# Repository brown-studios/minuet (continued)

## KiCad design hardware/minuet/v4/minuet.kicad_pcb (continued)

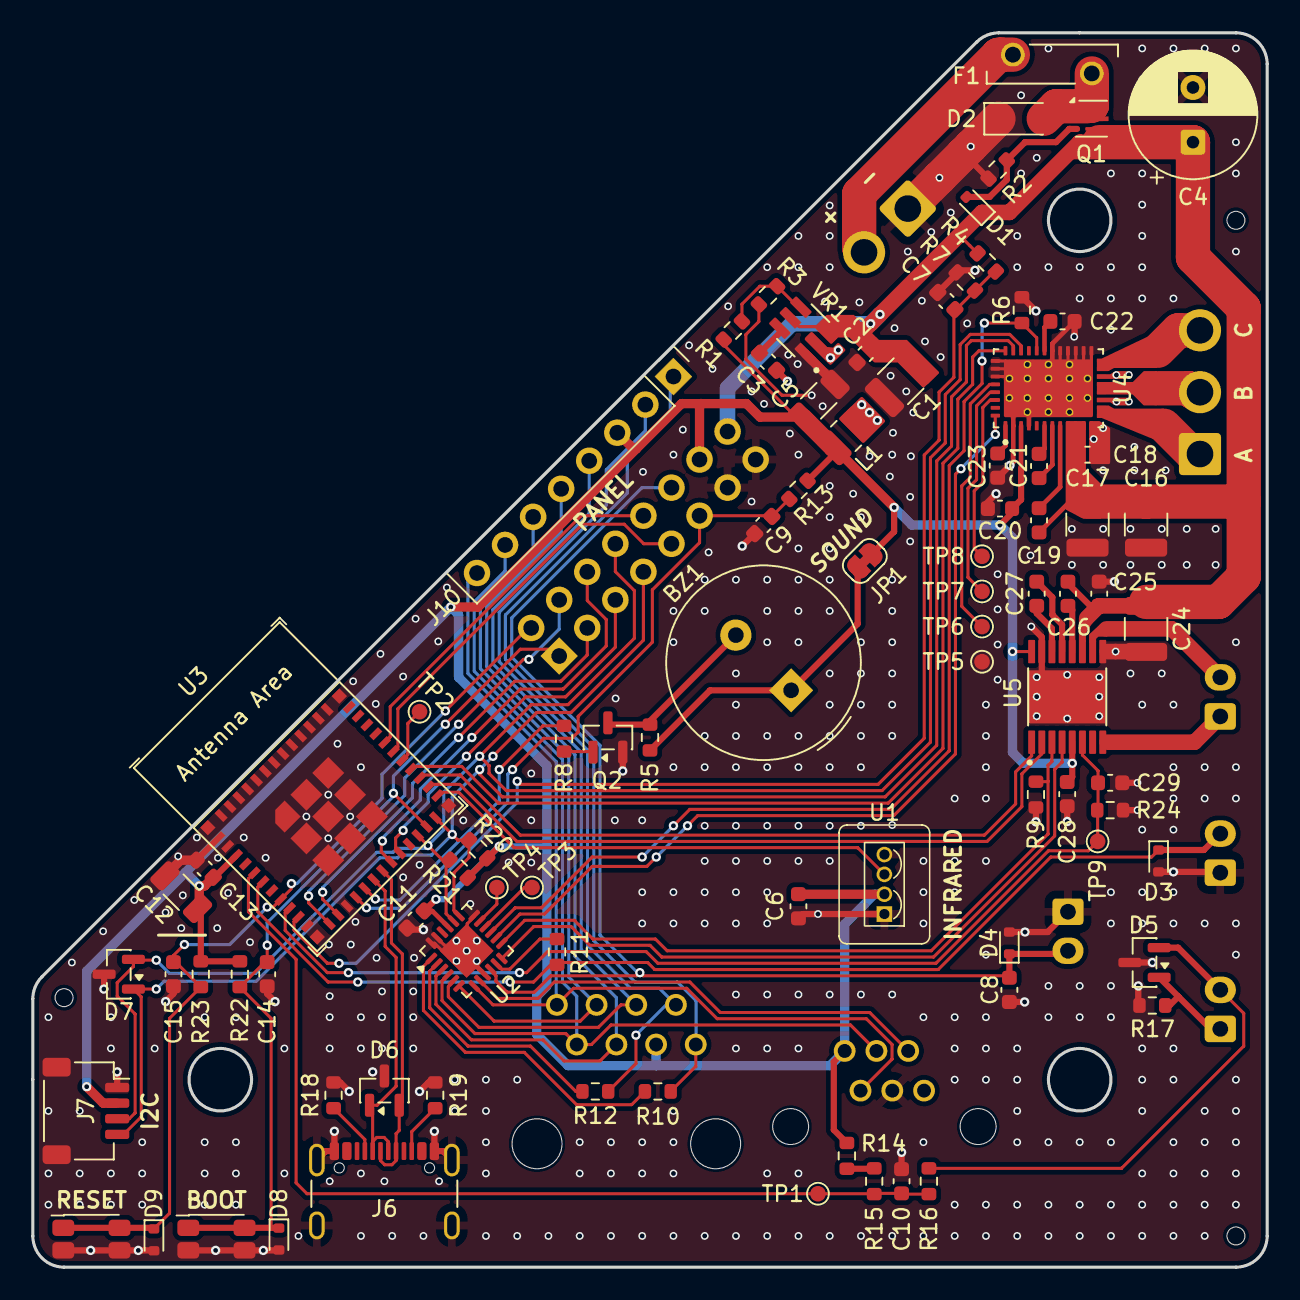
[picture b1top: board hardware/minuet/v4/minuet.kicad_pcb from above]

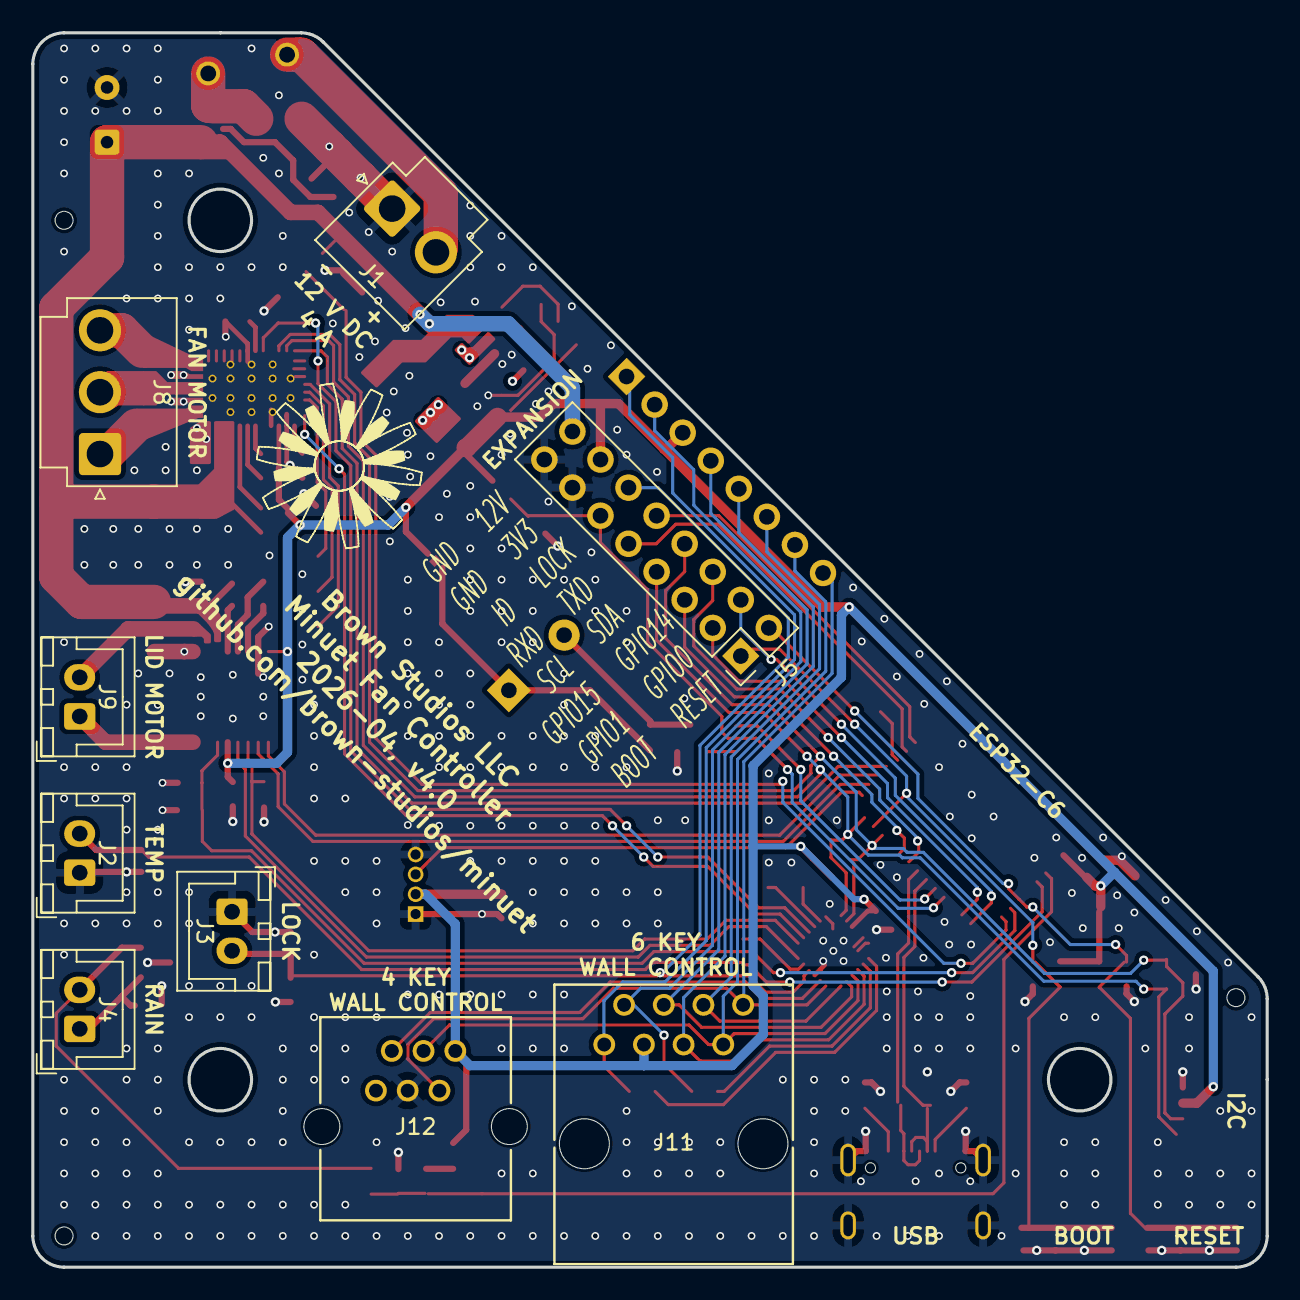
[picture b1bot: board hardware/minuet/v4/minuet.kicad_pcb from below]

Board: 4 copper layers, 79.0 x 79.0 mm, 103 parts (9 on the bottom side), 77 nets.

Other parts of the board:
TH1, TH2, TH3: JLCPCB_PCBA_Tooling_Hole

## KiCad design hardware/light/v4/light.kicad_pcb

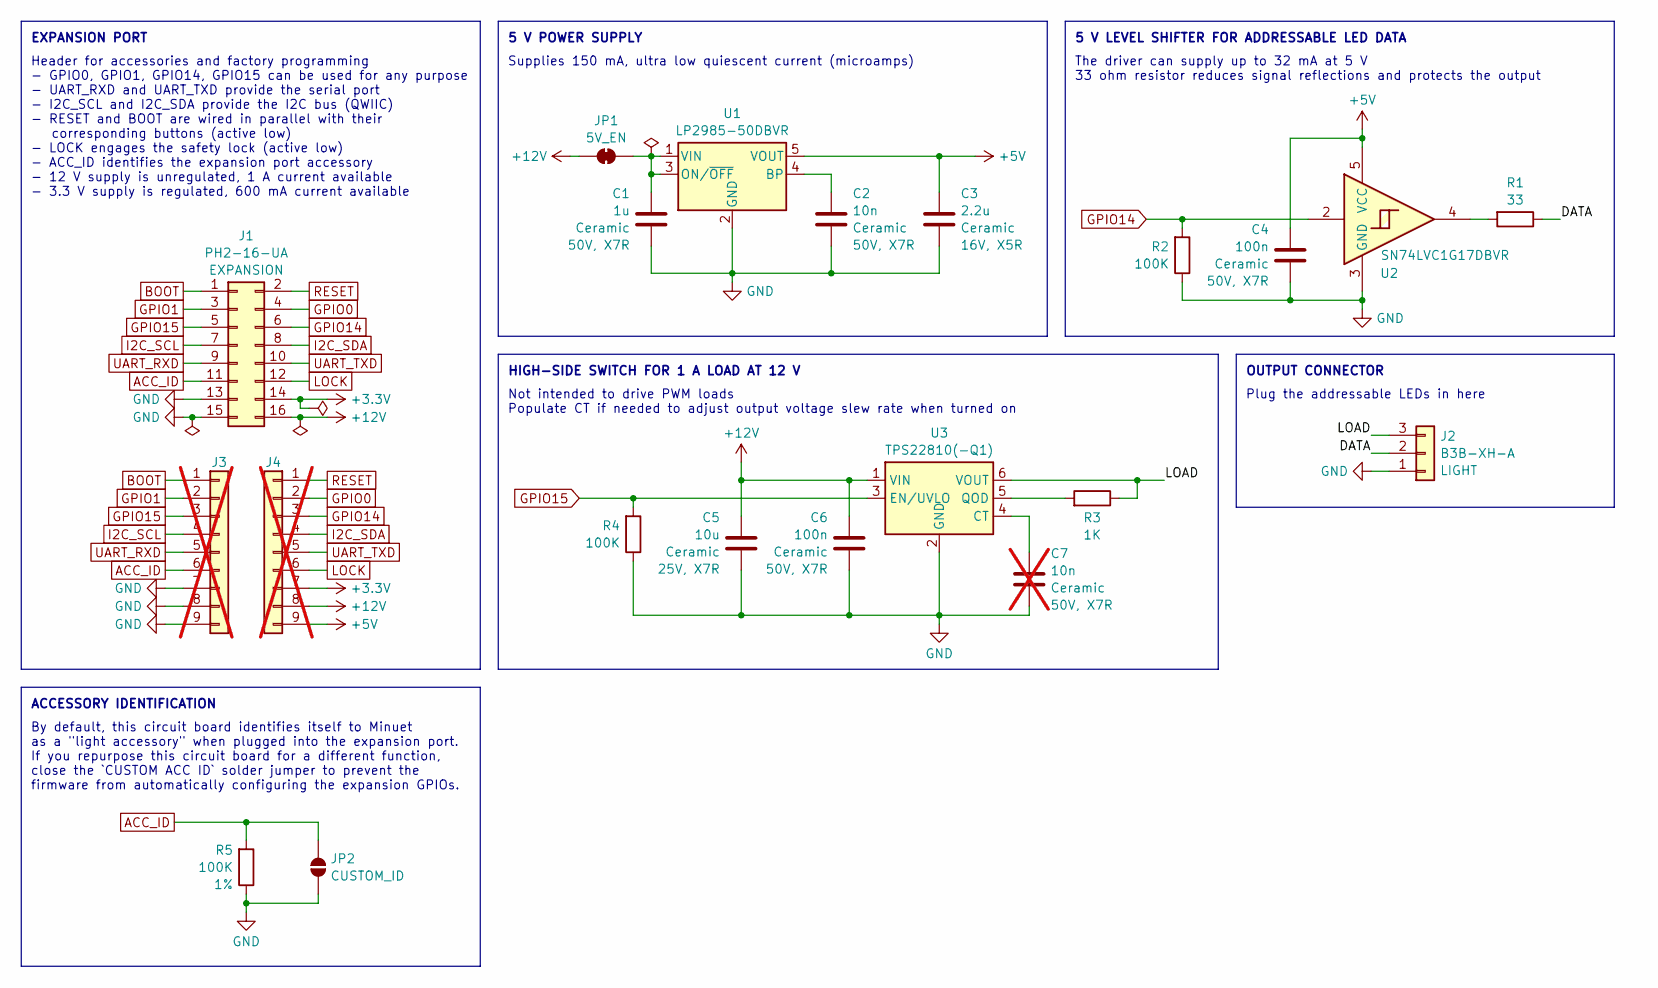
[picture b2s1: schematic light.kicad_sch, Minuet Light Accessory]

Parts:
C1: 1u; C_0805_2012Metric; Rating 50V, X7R; LCSC C28323
C2: 10n; C_0603_1608Metric; Rating 50V, X7R; LCSC C57112
C3: 2.2u; C_0603_1608Metric; Rating 16V, X5R; LCSC C23630
C4, C6: 100n; C_0603_1608Metric; Rating 50V, X7R; LCSC C14663
C5: 10u; C_1210_3225Metric; Rating 25V, X7R; Part CL32B106KAJNNNE; LCSC C39232
C7: 10n; C_0603_1608Metric; Rating 50V, X7R; LCSC C57112; not fitted
J1: PH2-16-UA; PinHeader_2x08_P2.54mm_Vertical; LCSC C492425
J2: B3B-XH-A; JST_XH_B3B-XH-A_1x03_P2.50mm_Vertical; LCSC C144394
J3, J4: Conn_01x09; Pins_1x09; not fitted
JP1: SolderJumper_2_Open; SolderJumper-2_P1.3mm_Bridged_RoundedPad1.0x1.5mm
JP2: SolderJumper_2_Open; SolderJumper-2_P1.3mm_Open_RoundedPad1.0x1.5mm
R1: 33; R_0603_1608Metric; Rating 1%; LCSC C23140
R2, R4, R5: 100K; R_0603_1608Metric; Rating 1%; LCSC C25803
R3: 1K; R_0603_1608Metric; Rating 1%; LCSC C21190
U1: LP2985-50DBVR; SOT-23-5; LCSC C74511
U2: SN74LVC1G17DBVR; SOT-23-5; LCSC C7836
U3: TPS22810(-Q1); SOT-23-6; LCSC C2877634

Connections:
+3.3V: J1.14, J4.7
+5V: C3.2, C4.1, J4.9, U1.5 (VOUT), U2.5 (VCC)
+12V: C5.1, C6.1, J1.16, J4.8, JP1.2 (B), U3.1 (VIN)
/DATA: J2.2, R1.1
/LOAD: J2.3, R3.1, U3.6 (VOUT)
ACC_ID: J1.11, J3.6, JP2.1 (A), R5.2
BOOT: J1.1, J3.1
GND: C1.2, C2.1, C3.1, C4.2, C5.2, C6.2, C7.1, J1.13, J1.15, J2.1, J3.7, J3.8, J3.9, JP2.2 (B), R2.1, R4.1, R5.1, U1.2 (GND), U2.3 (GND), U3.2 (GND)
GPIO0: J1.4, J4.2
GPIO1: J1.3, J3.2
GPIO14: J1.6, J4.3, R2.2, U2.2
GPIO15: J1.5, J3.3, R4.2, U3.3 (EN/UVLO)
I2C_SCL: J1.7, J3.4
I2C_SDA: J1.8, J4.4
LOCK: J1.12, J4.6
unnamed: C1.1, JP1.1 (A), U1.1 (VIN), U1.3 (ON/~OFF)
unnamed: R1.2, U2.4
unnamed: C2.2, U1.4 (BP)
unnamed: C7.2, U3.4 (CT)
unnamed: R3.2, U3.5 (QOD)
RESET: J1.2, J4.1
UART_RXD: J1.9, J3.5
UART_TXD: J1.10, J4.5

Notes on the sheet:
HIGH-SIDE SWITCH FOR 1 A LOAD AT 12 V
Not intended to drive PWM loads Populate CT if needed to adjust output voltage slew rate when turned on
Plug the addressable LEDs in here
The driver can supply up to 32 mA at 5 V 33 ohm resistor reduces signal reflections and protects the output
By default, this circuit board identifies itself to Minuet as a "light accessory" when plugged into the expansion port. If you repurpose this circuit board for a different function, close the `CUSTOM ACC ID` solder jumper to prevent the firmware from automatically configuring the expansion GPIOs.
ACCESSORY IDENTIFICATION
Header for accessories and factory programming - GPIO0, GPIO1, GPIO14, GPIO15 can be used for any purpose - UART_RXD and UART_TXD provide the serial port - I2C_SCL and I2C_SDA provide the I2C bus (QWIIC) - RESET and BOOT are wired in parallel with their corresponding buttons (active low) - LOCK eng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
5 V LEVEL SHIFTER FOR ADDRESSABLE LED DATA
EXPANSION PORT
Supplies 150 mA, ultra low quiescent current (microamps)
5 V POWER SUPPLY
OUTPUT CONNECTOR

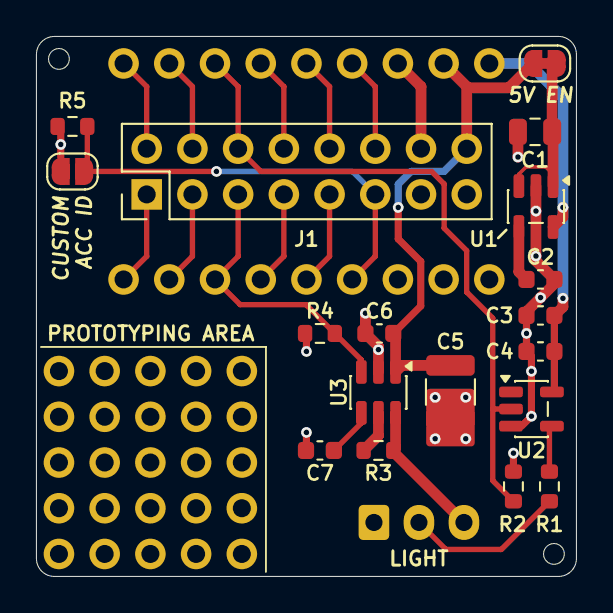
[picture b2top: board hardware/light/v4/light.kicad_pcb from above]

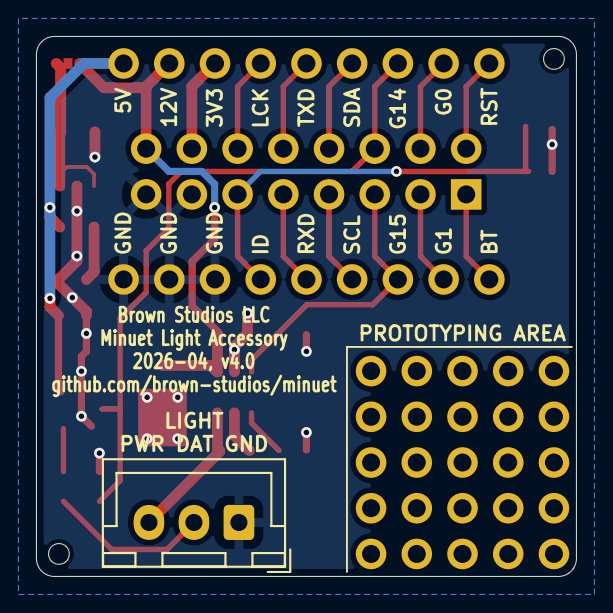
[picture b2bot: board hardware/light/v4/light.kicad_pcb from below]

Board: 2 copper layers, 30.0 x 30.0 mm, 24 parts (3 on the bottom side), 23 nets.

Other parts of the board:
PROTO: Val**; ProtoPins
TH1, TH2: JLCPCB_PCBA_Tooling_Hole

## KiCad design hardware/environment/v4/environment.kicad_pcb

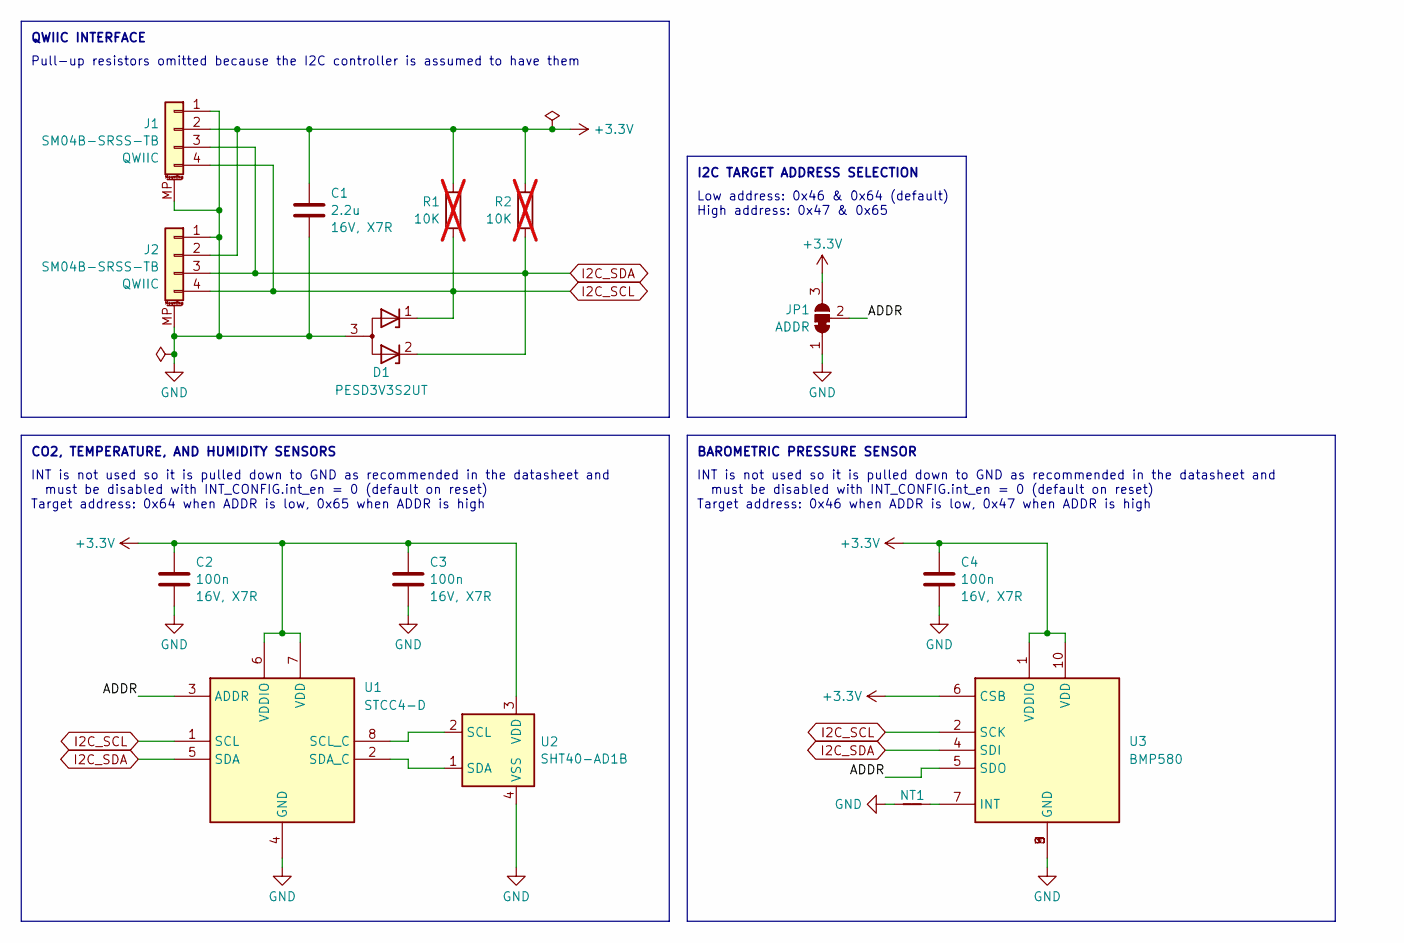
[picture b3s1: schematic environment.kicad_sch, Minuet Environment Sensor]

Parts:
C1: 2.2u; C_0805_2012Metric; Rating 16V, X7R; MPN CL21B225KOFNNNE; LCSC C28234
C2, C3, C4: 100n; C_0402_1005Metric; Rating 16V, X7R; MPN CL05B104KO5NNNC; LCSC C1525
D1: PESD3V3S2UT; SOT-23; LCSC C84276
J1, J2: SM04B-SRSS-TB; JST_SH_SM04B-SRSS-TB_1x04-1MP_P1.00mm_Horizontal; LCSC C160404
JP1: SolderJumper_3_Bridged12; SolderJumper-3_P1.3mm_Bridged12_RoundedPad1.0x1.5mm
NT1: NetTie_2; NetTie-2_SMD_Pad0.2mm
R1, R2: 10K; R_0402_1005Metric; Rating 1%; LCSC C25744; not fitted
U1: STCC4-D; STCC4; LCSC C49191471
U2: SHT40-AD1B; Sensirion_DFN-4_1.5x1.5mm_P0.8mm_SHT4x_NoCentralPad; LCSC C2848306
U3: BMP580; BMP581; LCSC C22391138

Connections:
+3.3V: C1.1, C2.1, C3.1, C4.1, J1.2, J2.2, JP1.3 (B), R1.1, R2.1, U1.6 (VDDIO), U1.7 (VDD), U2.3 (VDD), U3.1 (VDDIO), U3.6 (CSB), U3.10 (VDD)
/ADDR: JP1.2 (C), U1.3 (ADDR), U3.5 (SDO)
GND: C1.2, C2.2, C3.2, C4.2, D1.3 (A), J1.1, J1.MP (MountPin), J2.1, J2.MP (MountPin), JP1.1 (A), NT1.1, U1.4 (GND), U2.4 (VSS), U3.3 (GND), U3.8 (GND), U3.9 (GND)
I2C_SCL: D1.1 (K), J1.4, J2.4, R1.2, U1.1 (SCL), U3.2 (SCK)
I2C_SDA: D1.2 (K), J1.3, J2.3, R2.2, U1.5 (SDA), U3.4 (SDI)
unnamed: U1.8 (SCL_C), U2.2 (SCL)
unnamed: U1.2 (SDA_C), U2.1 (SDA)
unnamed: NT1.2, U3.7 (INT)

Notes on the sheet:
INT is not used so it is pulled down to GND as recommended in the datasheet and must be disabled with INT_CONFIG.int_en = 0 (default on reset) Target address: 0x64 when ADDR is low, 0x65 when ADDR is high
Pull-up resistors omitted because the I2C controller is assumed to have them
QWIIC INTERFACE
Low address: 0x46 & 0x64 (default) High address: 0x47 & 0x65
BAROMETRIC PRESSURE SENSOR
CO2, TEMPERATURE, AND HUMIDITY SENSORS
I2C TARGET ADDRESS SELECTION
INT is not used so it is pulled down to GND as recommended in the datasheet and must be disabled with INT_CONFIG.int_en = 0 (default on reset) Target address: 0x46 when ADDR is low, 0x47 when ADDR is high

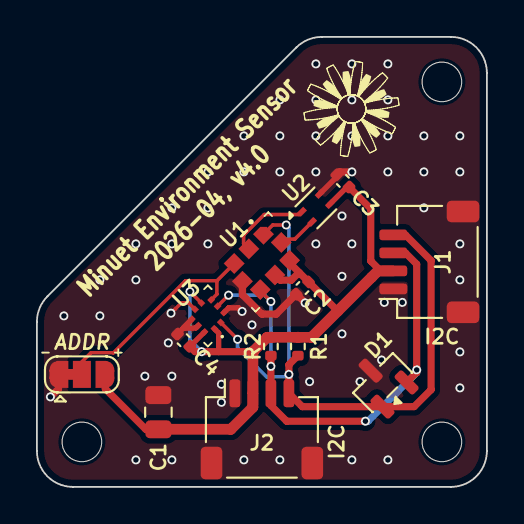
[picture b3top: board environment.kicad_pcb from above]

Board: 4 copper layers, 25.0 x 25.0 mm, 17 parts (0 on the bottom side), 8 nets.

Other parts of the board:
H1, H1#2, H1#3: MountingHole_2.2mm_M2

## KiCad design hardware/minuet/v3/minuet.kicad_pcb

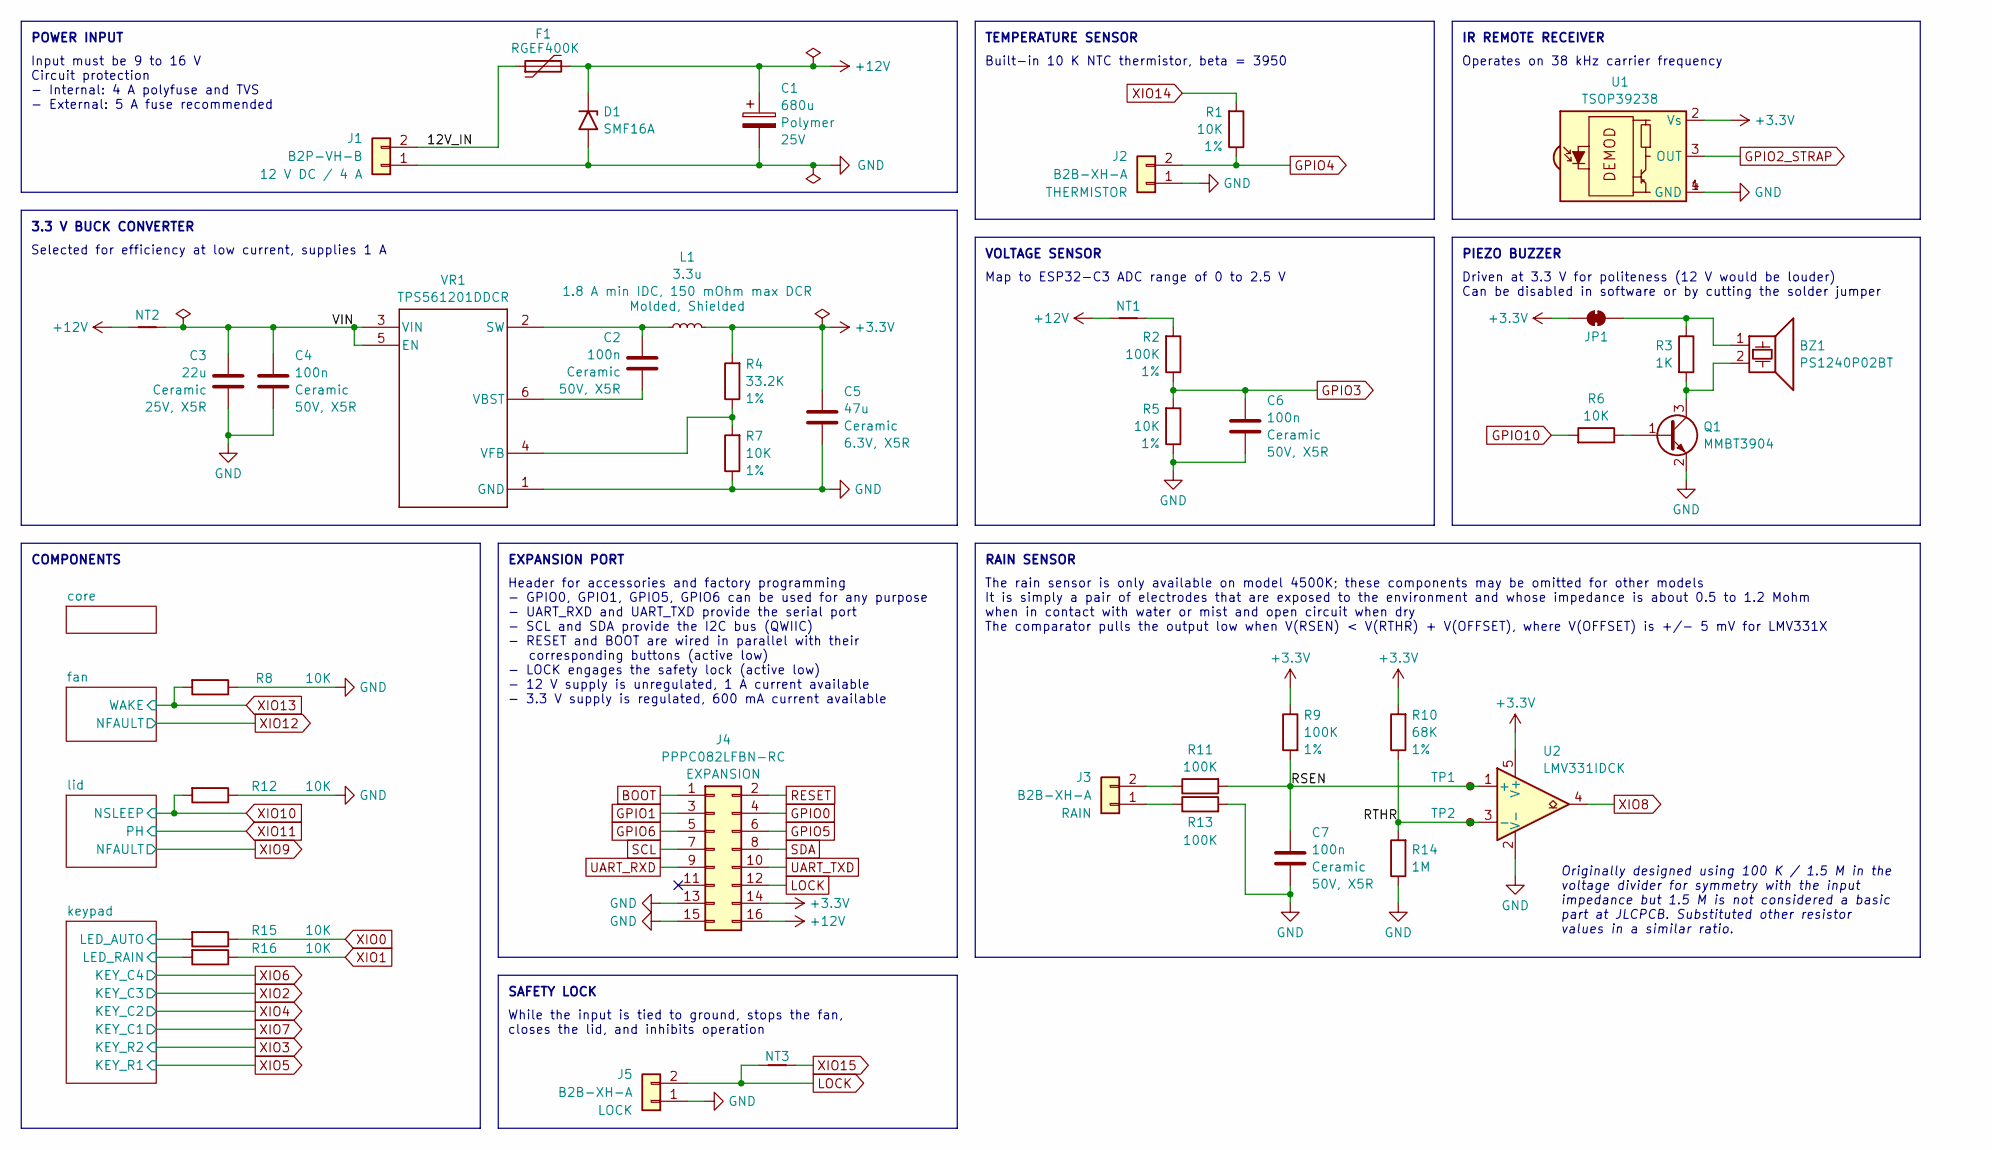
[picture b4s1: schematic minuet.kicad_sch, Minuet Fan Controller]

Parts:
BZ1: PS1240P02BT; Buzzer_TDK_PS1240P02BT_D12.2mm_H6.5mm; LCSC C76871
C1: 680u; CP_Radial_D8.0mm_P3.50mm; Rating 25V; LCSC C5243855
C2, C4, C6, C7: 100n; C_0603_1608Metric; Rating 50V, X5R; LCSC C14663
C3: 22u; C_0805_2012Metric; Rating 25V, X5R; LCSC C45783
C5: 47u; C_0805_2012Metric; Rating 6.3V, X5R; LCSC C16780
D1: SMF16A; D_SMF; LCSC C207257
F1: RGEF400K; LCSC C135392
J1: B2P-VH-B; JST_VH_B2P-VH-B_1x02_P3.96mm_Vertical; LCSC C265114
J2, J3, J5: B2B-XH-A; JST_XH_B2B-XH-A_1x02_P2.50mm_Vertical; LCSC C158012
J4: PPPC082LFBN-RC; PinSocket_2x08_P2.54mm_Vertical; LCSC C2897409
JP1: SolderJumper_2_Bridged; SolderJumper-2_P1.3mm_Bridged_RoundedPad1.0x1.5mm
L1: 3.3u; L_1008_2520Metric; Rating 1.8 A min IDC, 150 mOhm max DCR; Part AOTA-B252010S3R3MT; LCSC C22416628
NT1, NT3: NetTie_2; NetTie-2_SMD_Pad0.2mm
NT2: NetTie_2; NetTie-2_SMD_Pad1.0mm
Q1: MMBT3904; SOT-23; LCSC C20526
R1, R5, R7: 10K; R_0603_1608Metric; Rating 1%; LCSC C25804
R2, R9: 100K; R_0603_1608Metric; Rating 1%; LCSC C25803
R3: 1K; R_0603_1608Metric; LCSC C21190
R4: 33.2K; R_0603_1608Metric; Rating 1%; LCSC C4216
R6, R8, R12, R15, R16: 10K; R_0603_1608Metric; LCSC C25804
R10: 68K; R_0603_1608Metric; Rating 1%; LCSC C23231
R11, R13: 100K; R_0603_1608Metric; LCSC C25803
R14: 1M; R_0603_1608Metric; LCSC C22935
TP1, TP2: TestPoint_Small; TestPoint_Pad_D1.0mm
U1: TSOP39238; TSOP39238_Standoff; LCSC C7128407
U2: LMV331IDCK; SOT-353_SC-70-5; LCSC C7976
VR1: TPS561201DDCR; SOT95P280X110-6N; LCSC C220433

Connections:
+3.3V: C5.1, J4.14, JP1.1 (A), L1.1, R4.2, R9.1, R10.2, U1.2 (Vs), U2.5 (V+); also elsewhere on the board
+12V: C1.1, D1.1 (A1), F1.2, J4.16, NT1.1, NT2.1; also elsewhere on the board
/12V_IN: F1.1, J1.2
/RSEN: C7.1, R9.2, R11.2, TP1.1, U2.1 (+)
/RTHR: R10.1, R14.2, TP2.1, U2.3 (-)
/VIN: C3.1, C4.1, NT2.2, VR1.3 (VIN), VR1.5 (EN)
/keypad/LED_AUTO: R15.2; also elsewhere on the board
/keypad/LED_RAIN: R16.2; also elsewhere on the board
BOOT: J4.1; also elsewhere on the board
GND: C1.2, C3.2, C4.2, C5.2, C6.2, C7.2, D1.2 (A2), J1.1, J2.1, J4.13, J4.15, J5.1, Q1.2 (E), R5.1, R7.1, R8.1, R12.1, R13.2, R14.1, U1.1 (GND), U1.4 (GND), U2.2 (V-), VR1.1 (GND); also elsewhere on the board
GPIO0: J4.4; also elsewhere on the board
GPIO1: J4.3; also elsewhere on the board
GPIO2_STRAP: U1.3 (OUT); also elsewhere on the board
GPIO3: C6.1, R2.1, R5.2; also elsewhere on the board
GPIO4: J2.2, R1.1; also elsewhere on the board
GPIO5: J4.6; also elsewhere on the board
GPIO6: J4.5; also elsewhere on the board
GPIO10: R6.2; also elsewhere on the board
LOCK: J4.12, J5.2, NT3.2
unnamed: J3.1, R13.1
unnamed: J3.2, R11.1
unnamed: BZ1.1, JP1.2 (B), R3.1
unnamed: NT1.2, R2.2
unnamed: Q1.1 (B), R6.1
unnamed: BZ1.2, Q1.3 (C), R3.2
unnamed: C2.1, L1.2, VR1.2 (SW)
unnamed: C2.2, VR1.6 (VBST)
unnamed: R4.1, R7.2, VR1.4 (VFB)
RESET: J4.2; also elsewhere on the board
SCL: J4.7; also elsewhere on the board
SDA: J4.8; also elsewhere on the board
UART_RXD: J4.9; also elsewhere on the board
UART_TXD: J4.10; also elsewhere on the board
XIO0: R15.1; also elsewhere on the board
XIO1: R16.1; also elsewhere on the board
XIO8: U2.4; also elsewhere on the board
XIO10: R12.2; also elsewhere on the board
XIO13: R8.2; also elsewhere on the board
XIO14: R1.2; also elsewhere on the board
XIO15: NT3.1; also elsewhere on the board

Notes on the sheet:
RAIN SENSOR
VOLTAGE SENSOR
Driven at 3.3 V for politeness (12 V would be louder) Can be disabled in software or by cutting the solder jumper
POWER INPUT
3.3 V BUCK CONVERTER
EXPANSION PORT
Operates on 38 kHz carrier frequency
Originally designed using 100 K / 1.5 M in the voltage divider for symmetry with the input impedance but 1.5 M is not considered a basic part at JLCPCB. Substituted other resistor values in a similar ratio.
The rain sensor is only available on model 4500K; these components may be omitted for other models It is simply a pair of electrodes that are exposed to the environment and whose impedance is about 0.5 to 1.2 Mohm when in contact with water or mist and open circuit when dry The comparator pulls the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
Input must be 9 to 16 V Circuit protection - Internal: 4 A polyfuse and TVS - External: 5 A fuse recommended
Header for accessories and factory programming - GPIO0, GPIO1, GPIO5, GPIO6 can be used for any purpose - UART_RXD and UART_TXD provide the serial port - SCL and SDA provide the I2C bus (QWIIC) - RESET and BOOT are wired in parallel with their corresponding buttons (active low) - LOCK engages the s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
While the input is tied to ground, stops the fan, closes the lid, and inhibits operation
IR REMOTE RECEIVER
PIEZO BUZZER
Selected for efficiency at low current, supplies 1 A
TEMPERATURE SENSOR
Map to ESP32-C3 ADC range of 0 to 2.5 V
Built-in 10 K NTC thermistor, beta = 3950
SAFETY LOCK
COMPONENTS

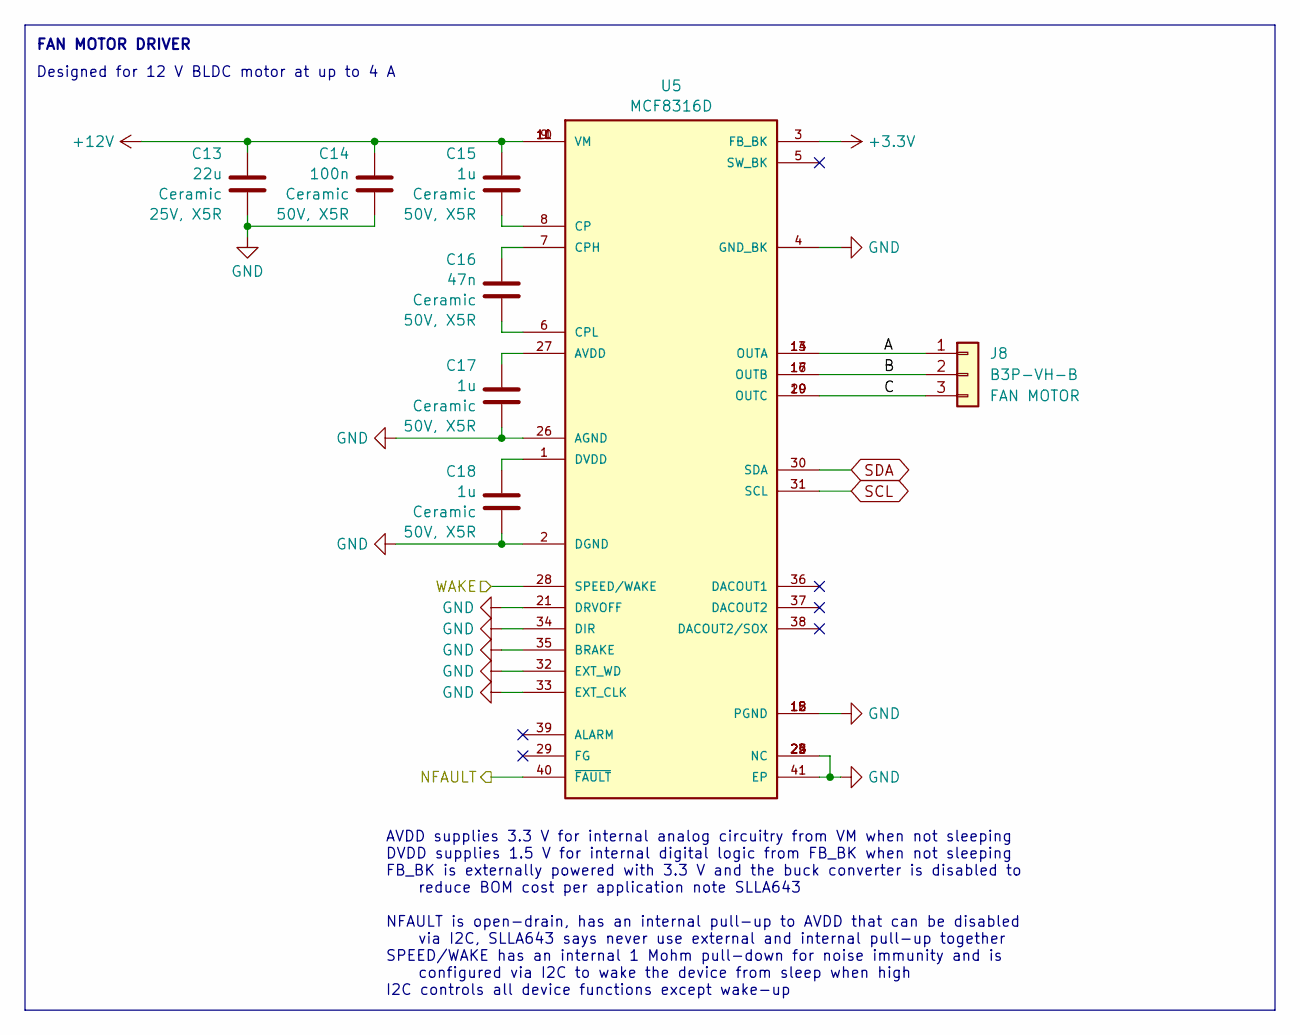
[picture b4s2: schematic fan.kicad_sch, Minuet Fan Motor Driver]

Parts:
C13: 22u; C_0805_2012Metric; Rating 25V, X5R; LCSC C45783
C14: 100n; C_0603_1608Metric; Rating 50V, X5R; LCSC C14663
C15, C17, C18: 1u; C_0603_1608Metric; Rating 50V, X5R; LCSC C15849
C16: 47n; C_0603_1608Metric; Rating 50V, X5R; LCSC C1622
J8: B3P-VH-B; JST_VH_B3P-VH-B_1x03_P3.96mm_Vertical; LCSC C265360
U5: MCF8316D; LCSC C42453588

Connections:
+3.3V: U5.3 (FB_BK); also elsewhere on the board
+12V: C13.1, C14.1, C15.1, U5.9 (VM), U5.10 (VM), U5.11 (VM); also elsewhere on the board
/fan/A: J8.1, U5.13 (OUTA), U5.14 (OUTA)
/fan/B: J8.2, U5.16 (OUTB), U5.17 (OUTB)
/fan/C: J8.3, U5.19 (OUTC), U5.20 (OUTC)
GND: C13.2, C14.2, C17.2, C18.2, U5.2 (DGND), U5.4 (GND_BK), U5.12 (PGND), U5.15 (PGND), U5.18 (PGND), U5.21 (DRVOFF), U5.22 (NC), U5.23 (NC), U5.24 (NC), U5.25 (NC), U5.26 (AGND), U5.32 (EXT_WD), U5.33 (EXT_CLK), U5.34 (DIR), U5.35 (BRAKE), U5.41 (EP); also elsewhere on the board
unnamed: C17.1, U5.27 (AVDD)
unnamed: C15.2, U5.8 (CP)
unnamed: C16.1, U5.7 (CPH)
unnamed: C16.2, U5.6 (CPL)
unnamed: C18.1, U5.1 (DVDD)
SCL: U5.31 (SCL); also elsewhere on the board
SDA: U5.30 (SDA); also elsewhere on the board
XIO12: U5.40 (~FAULT); also elsewhere on the board
XIO13: U5.28 (SPEED/WAKE); also elsewhere on the board

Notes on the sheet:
FAN MOTOR DRIVER
Designed for 12 V BLDC motor at up to 4 A
AVDD supplies 3.3 V for internal analog circuitry from VM when not sleeping DVDD supplies 1.5 V for internal digital logic from FB_BK when not sleeping FB_BK is externally powered with 3.3 V and the buck converter is disabled to reduce BOM cost per application note SLLA643 NFAULT is open-drain, has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

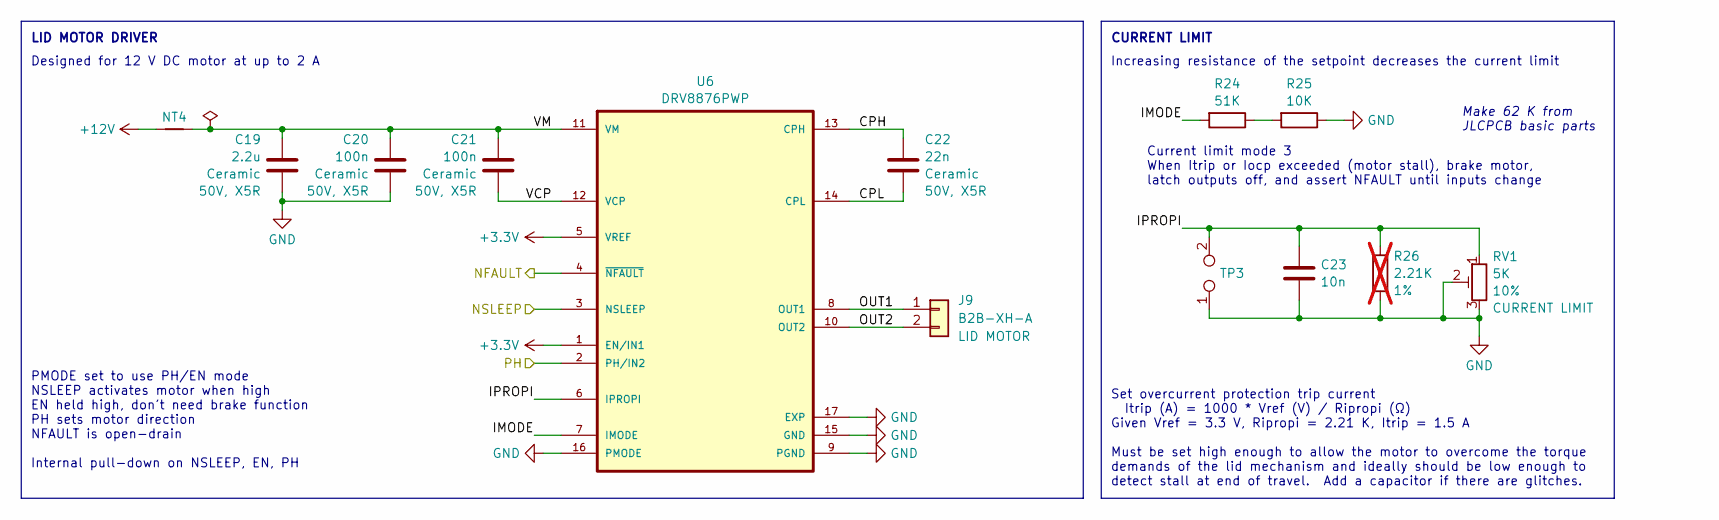
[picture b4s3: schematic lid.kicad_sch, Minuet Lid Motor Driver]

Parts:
C19: 2.2u; C_0805_2012Metric; Rating 50V, X5R; LCSC C377773
C20, C21: 100n; C_0603_1608Metric; Rating 50V, X5R; LCSC C14663
C22: 22n; C_0603_1608Metric; Rating 50V, X5R; LCSC C21122
C23: 10n; C_0603_1608Metric; Rating 50V, X5R; LCSC C57112
J9: B2B-XH-A; JST_XH_B2B-XH-A_1x02_P2.50mm_Vertical; LCSC C158012
NT4: NetTie_2; NetTie-2_SMD_Pad1.0mm
R24: 51K; R_0603_1608Metric; LCSC C23196
R25: 10K; R_0603_1608Metric; LCSC C25804
R26: 2.21K; R_0603_1608Metric; Rating 1%; not fitted
RV1: 5K; TRIM_3362P-1-502LF; Rating 10%; LCSC C81260
TP3: TestPoint_2Pole; TestPoint_2Pads_Pitch2.54mm_Drill0.8mm
U6: DRV8876PWP; IC_DRV8876PWPR; LCSC C575551

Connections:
+3.3V: U6.1 (EN/IN1), U6.5 (VREF); also elsewhere on the board
+12V: NT4.1; also elsewhere on the board
/lid/CPH: C22.1, U6.13 (CPH)
/lid/CPL: C22.2, U6.14 (CPL)
/lid/IMODE: R24.2, U6.7 (IMODE)
/lid/IPROPI: C23.1, R26.1, RV1.1, TP3.2, U6.6 (IPROPI)
/lid/OUT1: J9.1, U6.8 (OUT1)
/lid/OUT2: J9.2, U6.10 (OUT2)
/lid/VCP: C21.2, U6.12 (VCP)
/lid/VM: C19.2, C20.1, C21.1, NT4.2, U6.11 (VM)
GND: C19.1, C20.2, C23.2, R25.1, R26.2, RV1.2, RV1.3, TP3.1, U6.9 (PGND), U6.15 (GND), U6.16 (PMODE), U6.17 (EXP); also elsewhere on the board
unnamed: R24.1, R25.2
XIO9: U6.4 (~NFAULT); also elsewhere on the board
XIO10: U6.3 (NSLEEP); also elsewhere on the board
XIO11: U6.2 (PH/IN2); also elsewhere on the board

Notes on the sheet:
Set overcurrent protection trip current Itrip (A) = 1000 * Vref (V) / Ripropi (Ω) Given Vref = 3.3 V, Ripropi = 2.21 K, Itrip = 1.5 A Must be set high enough to allow the motor to overcome the torque demands of the lid mechanism and ideally should be low enough to detect stall at end of travel. Add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
Increasing resistance of the setpoint decreases the current limit
CURRENT LIMIT
PMODE set to use PH/EN mode NSLEEP activates motor when high EN held high, don't need brake function PH sets motor direction NFAULT is open-drain Internal pull-down on NSLEEP, EN, PH
Designed for 12 V DC motor at up to 2 A
Make 62 K from JLCPCB basic parts
LID MOTOR DRIVER
Current limit mode 3 When Itrip or Iocp exceeded (motor stall), brake motor, latch outputs off, and assert NFAULT until inputs change
